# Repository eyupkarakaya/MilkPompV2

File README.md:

# Milk Pomp
Proje, kullanicinin farkli tip ve hacimli bardaklara makineden süt doldurmak için kullanilacak bir cihazin kontrol kartinin tasarlanmasi işidir.

Cihazın mekanik tasarımı, flow sensör ve pompa seçimi müşteri tarafından hazırlanmıştır. Bizim yapacağımız iş ise sistemin çalışmasını sağlayacak elektronik kontrol kartının tasarlanmasıdır.

## Sistemin Çalismasi
Cihaz maksimum 9 farklı bardak bilgisini hafızada tutabilir. Kullanıcı bardak seçimi yaparak kayıtlı bardak tiplerinden birini otomatik olarak doldurabilir. Fakat istenirse kayıtlı olmayan farklı bir kabı da manuel olarak istediği miktarda doldurabilir.

Cihaz üzerinde 3 adet buton ve 1 adet 7-Segment gösterge bulunmaktadır. Ayrıca, bir pulse girişi ile **Akış Sensoru** girişi okunacak ve çıkış olarak bir role kontrol edilecektir.

	* I/O (On/Off) butonu
	* Start butonu
	* Mode butonu
	* Akış Sensoru (Encoder Pulse Input)
	* Role

Aşağıda tarif edilen çalışma şekilleri bu 3 buton ve gösterge kullanılarak gerçeklenecektir.

Sistemi çalıştırmak için I/O butonuna bir kere basıp bırakmak yeterlidir. Sistem kapalıyken gösterge ve diğer butonlar aktif değildir. I/O butonuna bir kere basılıp bırakıldığında sistem açılır, eğer kalibrasyon yapılmamışsa (hiç bardak tanımı yoksa) **C.** değeri görünür ve ekran yanıp söner. Aksi halde sabit olarak **0** yazar ve bardak seçimi için bekler.

Cihaz 3 farklı çalışma şekline sahip olacaktır.

### Kalibrasyon
Kalibrasyon modu, elimizde bulunan bardakların tanımlanması için kullanılır. Maksimum 9 farklı bardak tanımı yapılabilir.

Kalibrasyon modu bir adet bardak tanıtmak istenirse aşağıdaki algoritmaya göre çalışır

	1- Kalibrasyonu başlatmak için I/O butonuna 5 saniye basılı tutulur
	2- Gösterge 0 değerini gösterir ve nokta yanıp sönmeye başlar
	3- İstenilen bardak, cihazın bardak bölmesine yerleştirilir
	4- Mode butonu ile bardak seçimi yapılır (1, 2, 3, ..)
	5- Start butonuna basılı tutularak bardak doldurulur
	6- Bardak dolunca Start butonu bırakılır
	7- Start butonu bırakıldığında seçilen bardak ve doldurulan miktar bilgileri otomatik olarak kaydedilir
	8- Kalibrasyon modundan çıkmak için I/O butonuna 5 saniye bayunca basılır
	
Eğer birden fazla bardak tanımı yapılmak istenirse yukarıdaki algoritma basamaklarından 1 nolu adım ile kalibrasyon işlemi başlatılır. 2-7 adımları her bir bardak için tekrarlanır. Tüm bardakların tanımlanma işlemi bittiğinde 8 nolu adım ile kalibrasyon işlemi sonlandırılır.

Daha sonra tanımlı bir bardağın kalibrasyonu değiştirilmek istendiğinde veya yeni bir bardak tanımı yapılması gerektiğinde yukarıdaki algoritma tekrar uygulanabilir.

> Dikkat edilmesi gereken nokta, eğer bardak tanımları yapılmış bir cihazda tek bir bardağın kalibrasyonu değiştirlmek istenirse, Mode butonu ile doğru bardak numarasının seçildiğinden emin olunması gerekmektedir.

### Otomatik Mod
Kalibrasyonu yapılmış bir cihazda kullanıcı bardak seçimi yaparak tanımlı bardaklardan birini otomatik olarak doldurabilir.

	1- İstenilen bardak, cihazın bardak bölmesine yerleştirilir
	2- Mode butonu kullanılarak bardak seçimi yapılır
	3- Start butonuna basılıp bırakıldığında tanımlı miktar kadar dolum yapılır
	
Her bir bardak için yukarıdaki adımlar tekrarlanır.

### Manuel Mod
Kalibrasyon yapılarak tanımlanmamış bir bardak veya farklı bir kap doldurulmak istendiğinde Manuel mod kullanılır.

    1- Doldurulmak istenilen kap yerleştirilir.
	2- Start butonuna basılı tutulur. Butona basıldıktan 5 saniye sonra manuel dolum başlar
	3- Kullanıcı Start butonunu bıraktığında dolum işlemi sonlanır.

## Kaynak/Arastirmalar
- [Flow Sensor](https://www.hepsiburada.com/fluidotech-kahve-makinasi-pompasi-rotary-pompa-pirinc-govdeli-p-HBV000007SB1Q)
- [Flow Sensor Kullanimi](https://how2electronics.com/iot-water-flow-meter-using-esp8266-water-flow-sensor/)
- [ESP8266 With Water Flow Sensor](https://www.14core.com/wiring-esp8266-1212e-with-g12-liquid-water-flow-sensor-for-wireless-monitoring/)

## Kullanilacak Bilesenler
- [STM32G030F6P6TR](docs/DS12991.pdf) 
- [Relay](http://www.omron.com/ecb/products/pdf/en-g5le.pdf)
- [Display](https://docs.broadcom.com/docs/AV02-2553EN)
- [TLP291](https://toshiba.semicon-storage.com/info/docget.jsp?did=12884&prodName=TLP291)
- Buttons
- Buzzer 
- Resistors
- Capasitors
- Transistors
- Leds
## Algoritma Adimlari
    1) Basla
	2) I/O Butonuna bir kere basarak sistemi ac (Diger hersey pasif olmali)
	3) Eger Kalibrasyon yapilmamissa C.yanip soner once kalibrasyon yapilmali. Eger Kalibrasyon yapilmissa 14.adima git(ilk acilis icin gecerli)
	4) Kalibrasyonu başlatmak için I/O butonuna 5 saniye basılı tutulur
	5) Gösterge 0 değerini gösterir ve nokta yanıp sönmeye başlar
	6) İstenilen bardak, cihazın bardak bölmesine yerleştirilir
	7) Mode butonu ile bardak seçimi yapılır (1, 2, 3, ..)
	8) Start butonuna basılı tutularak bardak doldurulur
	9) Bardak dolunca Start butonu bırakılır
	10) Start butonu bırakıldığında seçilen bardak ve doldurulan miktar bilgileri otomatik olarak kaydedilir
	11) Kalibrasyon modundan çıkmak için I/O butonuna 5 saniye bayunca basılır
	12) Max 9 bardak tanimlanibilir, tanimlanma islemi bittikten sonra 11 adimla islem tamamlanir
	13) Eger birden fazla bardak tanimi yapilmak istenilirse 4 adimdan baslayip 5-11 arasi adimlar tekrarlanir
	14) Eger kalibrasyon yapilmissa ekranda 0 yazar ve bekler
	15) Iki farkli sekilde bardak doldurabilir otomatik ve manuel biri secilir
	16) Eger otomatik ise islem soyle devam eder
	17) İstenilen bardak, cihazın bardak bölmesine yerleştirilir
	18) Mode butonu kullanılarak bardak seçimi yapılır(ornek 1.bardak 0-100ml alir,2.bardak 200-300ml alir)
	19) Start butonuna basılıp bırakıldığında tanımlı miktar kadar dolum yapılır her bardak icin islem tekrar edilir
	20) Eger manuel ise oldurulmak istenilen kap yerleştirilir
	21) Start butonuna basılı tutulur. Butona basıldıktan 5 saniye sonra manuel dolum başlar
	22) Kullanıcı Start butonunu bıraktığında dolum işlemi sonlanır
   
## Algoritma Akış Şeması

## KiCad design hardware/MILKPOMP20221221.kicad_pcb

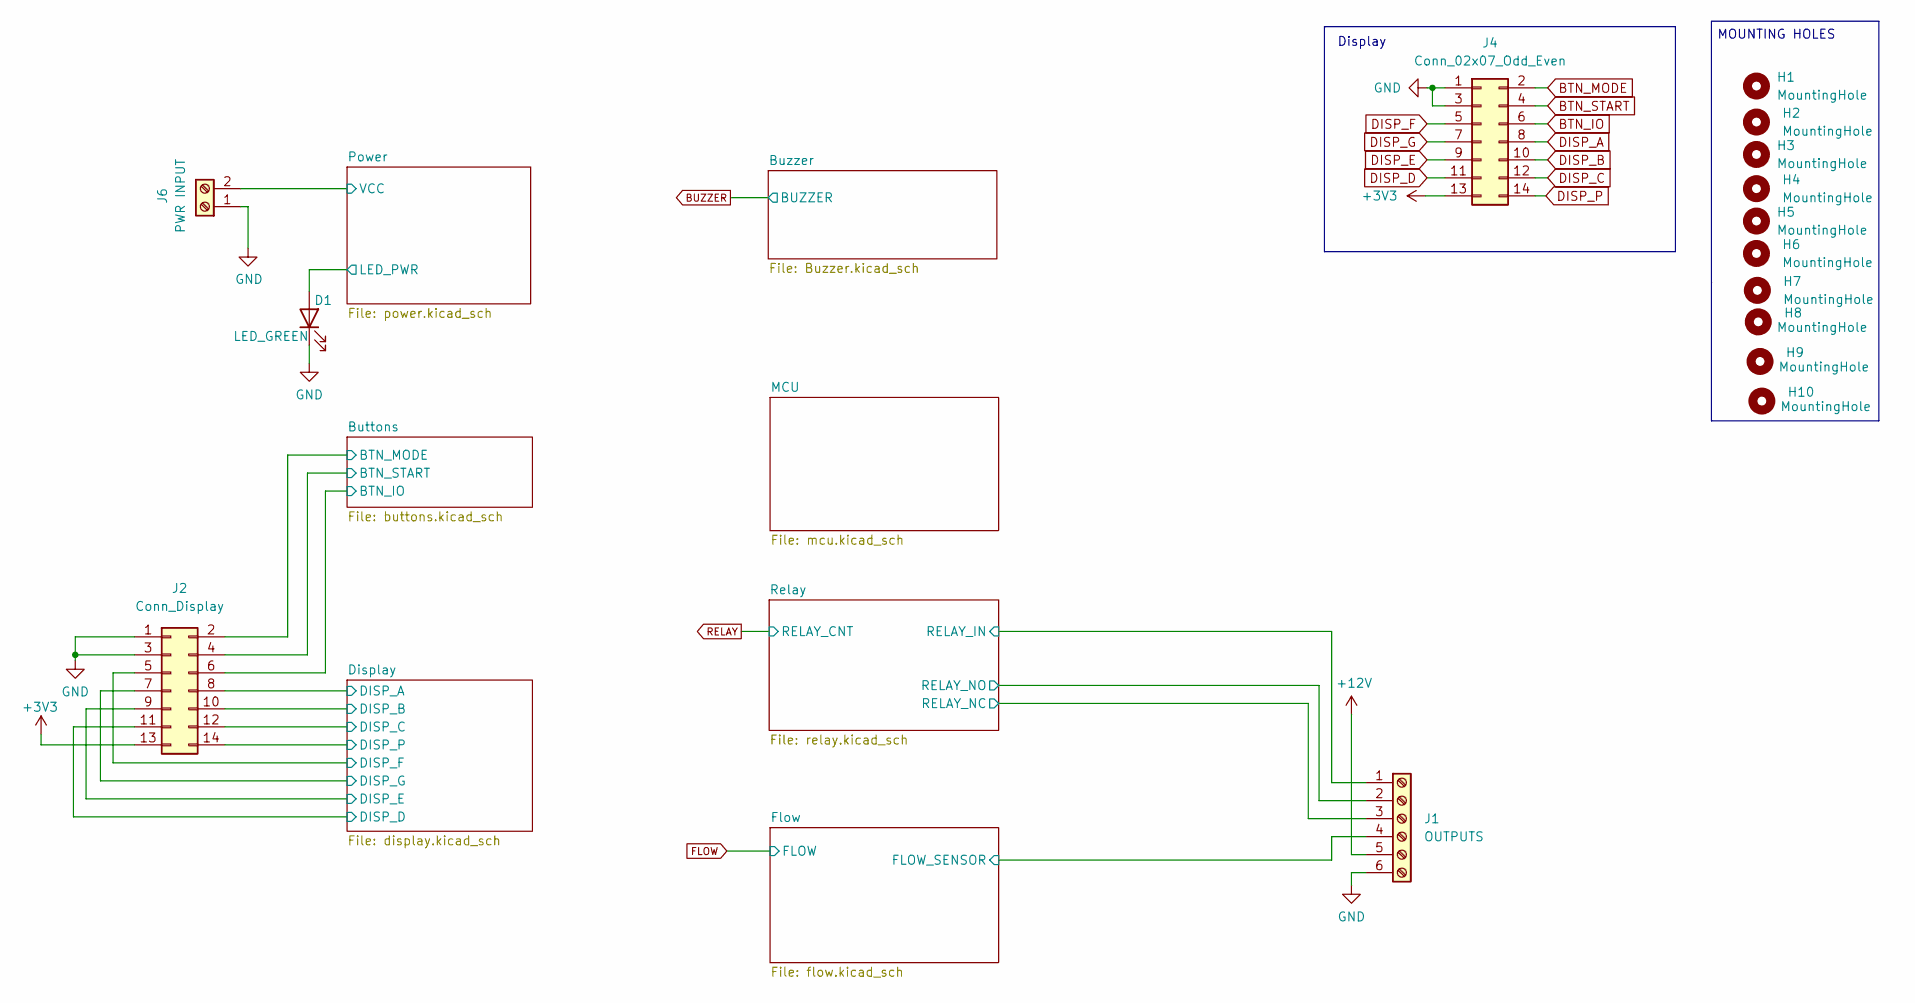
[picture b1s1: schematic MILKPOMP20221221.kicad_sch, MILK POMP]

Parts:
D1: LED_GREEN; LED_1206_3216Metric
H1, H2, H3, H4, H5, H6, H7, H8, H9, H10: MountingHole; MountingHole_2.5mm
J1: OUTPUTS; PhoenixContact_MSTBA_2,5_6-G-5,08_1x06_P5.08mm_Horizontal
J2: Conn_Display; Multicomp_MC9A12-1434_2x07x2.54mm_Straight
J4: Conn_02x07_Odd_Even; Multicomp_MC9A12-1434_2x07x2.54mm_Straight
J6: PWR INPUT; PhoenixContact_MSTBA_2,5_2-G_1x02_P5.00mm_Horizontal

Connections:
+3V3: J2.13, J4.13; also elsewhere on the board
+12V: J1.5, J6.2; also elsewhere on the board
/Buttons/BTN_IO: J2.6; also elsewhere on the board
/Buttons/BTN_MODE: J2.2; also elsewhere on the board
/Buttons/BTN_START: J2.4; also elsewhere on the board
/Display/DISP_A: J2.8; also elsewhere on the board
/Display/DISP_B: J2.10; also elsewhere on the board
/Display/DISP_C: J2.12; also elsewhere on the board
/Display/DISP_D: J2.11; also elsewhere on the board
/Display/DISP_E: J2.9; also elsewhere on the board
/Display/DISP_F: J2.5; also elsewhere on the board
/Display/DISP_G: J2.7; also elsewhere on the board
/Display/DISP_P: J2.14; also elsewhere on the board
/Flow/FLOW_SENSOR: J1.4; also elsewhere on the board
/Power/LED_PWR: D1.2 (A); also elsewhere on the board
/Relay /RELAY_IN: J1.1; also elsewhere on the board
/Relay /RELAY_NC: J1.3; also elsewhere on the board
/Relay /RELAY_NO: J1.2; also elsewhere on the board
BTN_IO: J4.6; also elsewhere on the board
BTN_MODE: J4.2; also elsewhere on the board
BTN_START: J4.4; also elsewhere on the board
DISP_A: J4.8; also elsewhere on the board
DISP_B: J4.10; also elsewhere on the board
DISP_C: J4.12; also elsewhere on the board
DISP_D: J4.11; also elsewhere on the board
DISP_E: J4.9; also elsewhere on the board
DISP_F: J4.5; also elsewhere on the board
DISP_G: J4.7; also elsewhere on the board
DISP_P: J4.14; also elsewhere on the board
GND: D1.1 (K), J1.6, J2.1, J2.3, J4.1, J4.3, J6.1; also elsewhere on the board

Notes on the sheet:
Display
MOUNTING HOLES

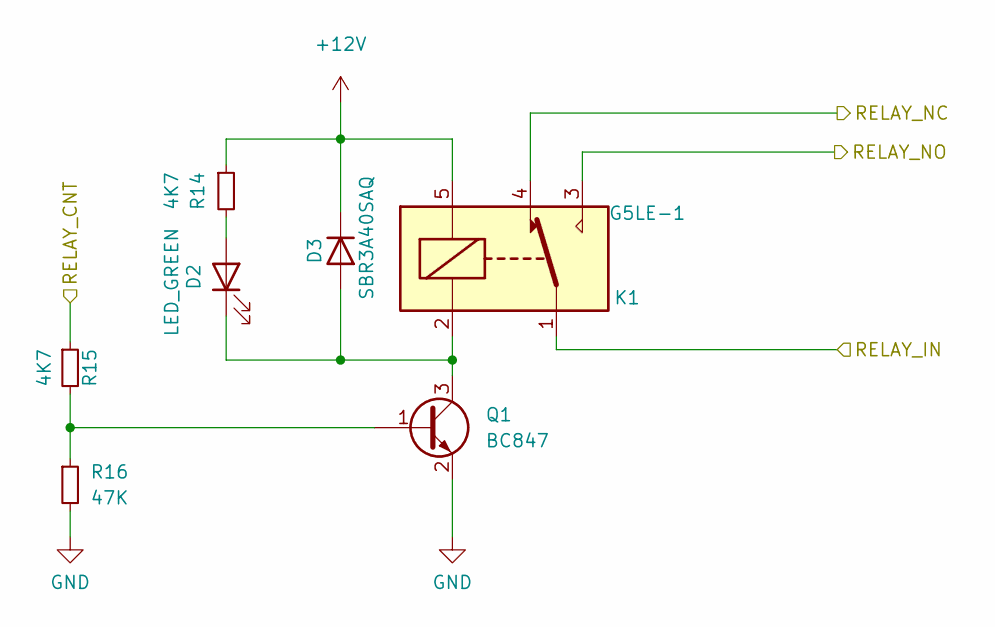
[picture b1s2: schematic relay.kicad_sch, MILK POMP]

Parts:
D2: LED_GREEN; LED_1206_3216Metric
D3: SBR3A40SAQ; D_SMB_Handsoldering; DIGIKEY_PART_NUMBER SBR3A40SAQ-13DICT-ND
K1: G5LE-1; Relay_SPDT_Omron-G5LE-1
Q1: BC847; SOT-23
R14, R15: 4K7; R_0603_1608Metric
R16: 47K; R_0603_1608Metric

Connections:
+12V: D3.1 (K), K1.5, R14.1; also elsewhere on the board
/Relay /RELAY_IN: K1.1; also elsewhere on the board
/Relay /RELAY_NC: K1.4; also elsewhere on the board
/Relay /RELAY_NO: K1.3; also elsewhere on the board
GND: Q1.2 (E), R16.2; also elsewhere on the board
unnamed: D2.1 (K), D3.2 (A), K1.2, Q1.3 (C)
unnamed: D2.2 (A), R14.2
unnamed: Q1.1 (B), R15.2, R16.1
RELAY: R15.1; also elsewhere on the board

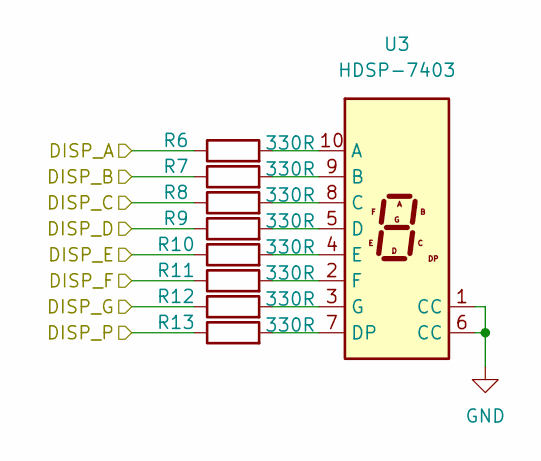
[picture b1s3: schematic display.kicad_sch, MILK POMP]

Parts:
R6, R7, R8, R9, R10, R11, R12, R13: 330R; R_0603_1608Metric
U3: HDSP-7403; HDSP-7401

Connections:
/Display/DISP_A: R6.1; also elsewhere on the board
/Display/DISP_B: R7.1; also elsewhere on the board
/Display/DISP_C: R8.1; also elsewhere on the board
/Display/DISP_D: R9.1; also elsewhere on the board
/Display/DISP_E: R10.1; also elsewhere on the board
/Display/DISP_F: R11.1; also elsewhere on the board
/Display/DISP_G: R12.1; also elsewhere on the board
/Display/DISP_P: R13.1; also elsewhere on the board
GND: U3.1 (CC), U3.6 (CC); also elsewhere on the board
unnamed: R6.2, U3.10 (A)
unnamed: R7.2, U3.9 (B)
unnamed: R8.2, U3.8 (C)
unnamed: R9.2, U3.5 (D)
unnamed: R10.2, U3.4 (E)
unnamed: R11.2, U3.2 (F)
unnamed: R12.2, U3.3 (G)
unnamed: R13.2, U3.7 (DP)

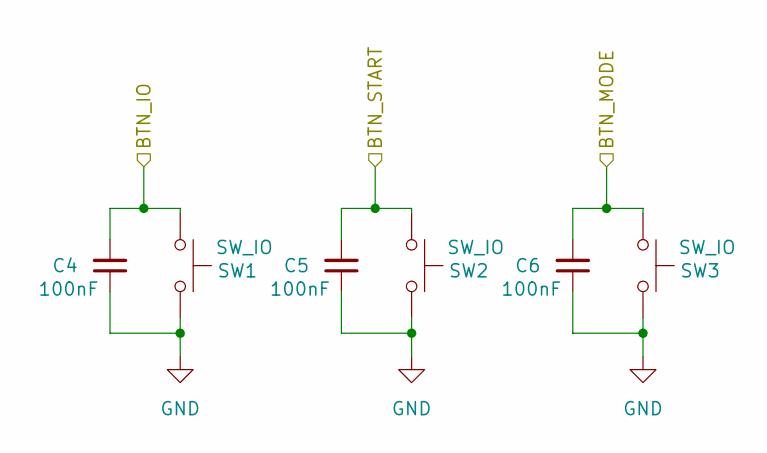
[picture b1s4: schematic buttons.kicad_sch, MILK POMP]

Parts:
C4, C5, C6: 100nF; C_0603_1608Metric
SW1, SW2, SW3: SW_IO; SW_PUSH-12mm

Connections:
/Buttons/BTN_IO: C4.2, SW1.1; also elsewhere on the board
/Buttons/BTN_MODE: C6.2, SW3.1; also elsewhere on the board
/Buttons/BTN_START: C5.2, SW2.1; also elsewhere on the board
GND: C4.1, C5.1, C6.1, SW1.2, SW2.2, SW3.2; also elsewhere on the board

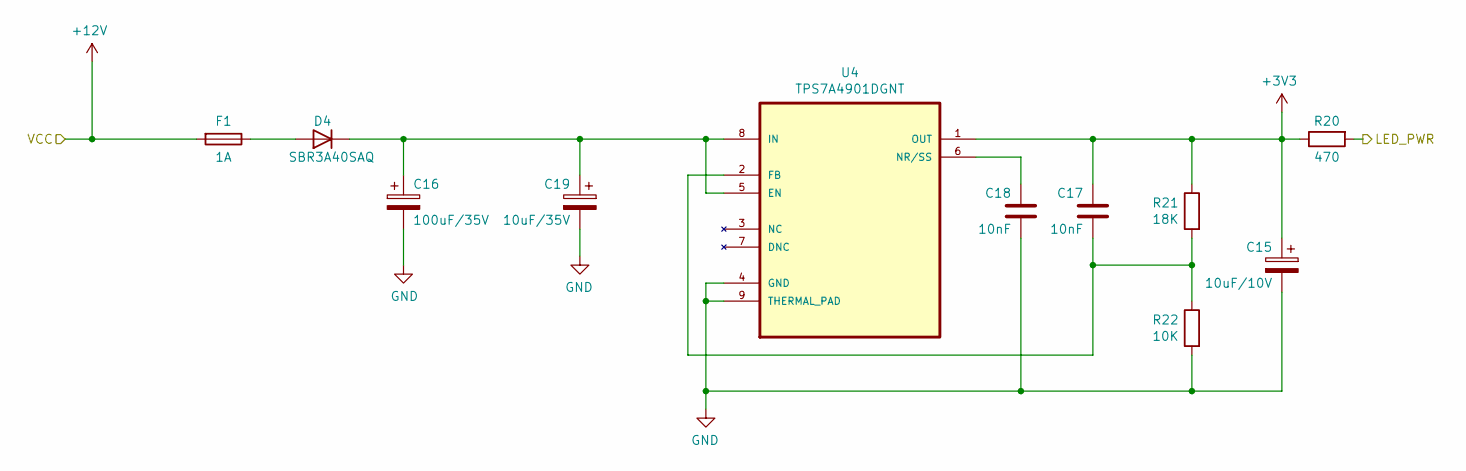
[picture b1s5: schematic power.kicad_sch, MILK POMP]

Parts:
C15: 10uF/10V; CP_Elec_6.3x7.7; Digikey 10-EEE-FN1A100RDKR-ND
C16: 100uF/35V; CP_Elec_10x10.5; Digikey PCE3951TR-ND
C17, C18: 10nF; C_0603_1608Metric; Digikey 1276-CL10B103KB8WPJCDKR-ND
C19: 10uF/35V; CP_Elec_6.3x7.7; Digikey 10-EEE-FN1A100RDKR-ND
D4: SBR3A40SAQ; D_SMB_Handsoldering; DIGIKEY_PART_NUMBER SBR3A40SAQ-13DICT-ND
F1: 1A; Fuse_1206_3216Metric; Digikey F2881CT-ND
R20: 470; R_0603_1608Metric; Digikey YAG1301DKR-ND
R21: 18K; R_0603_1608Metric; Digikey YAG3570DKR-ND
R22: 10K; R_0603_1608Metric; Digikey 311-10.0KHRDKR-ND
U4: TPS7A4901DGNT; SOP65P490X110-9N; MPN TPS7A4901DGNT; Digikey 296-27769-6-ND

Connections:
+3V3: C15.1, C17.1, R20.1, R21.1, U4.1 (OUT); also elsewhere on the board
+12V: F1.2; also elsewhere on the board
/Power/LED_PWR: R20.2; also elsewhere on the board
GND: C15.2, C16.2, C18.2, C19.2, R22.2, U4.4 (GND), U4.9 (THERMAL_PAD); also elsewhere on the board
unnamed: C16.1, C19.1, D4.1 (K), U4.5 (EN), U4.8 (IN)
unnamed: C17.2, R21.2, R22.1, U4.2 (FB)
unnamed: C18.1, U4.6 (NR/SS)
unnamed: D4.2 (A), F1.1

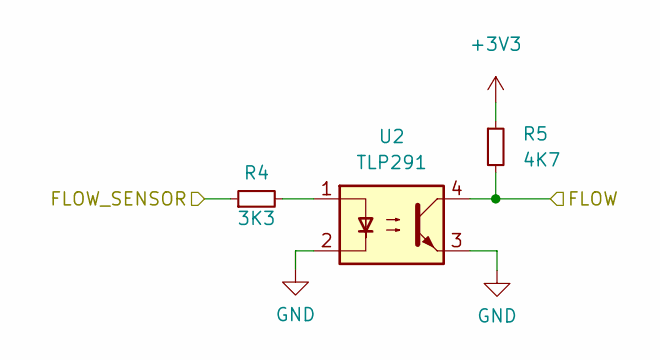
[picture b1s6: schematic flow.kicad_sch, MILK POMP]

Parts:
R4: 3K3; R_0603_1608Metric
R5: 4K7; R_0603_1608Metric
U2: TLP291; SOIC-4_4.55x2.6mm_P1.27mm

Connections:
+3V3: R5.1; also elsewhere on the board
/Flow/FLOW_SENSOR: R4.1; also elsewhere on the board
FLOW: R5.2, U2.4; also elsewhere on the board
GND: U2.2, U2.3; also elsewhere on the board
unnamed: R4.2, U2.1

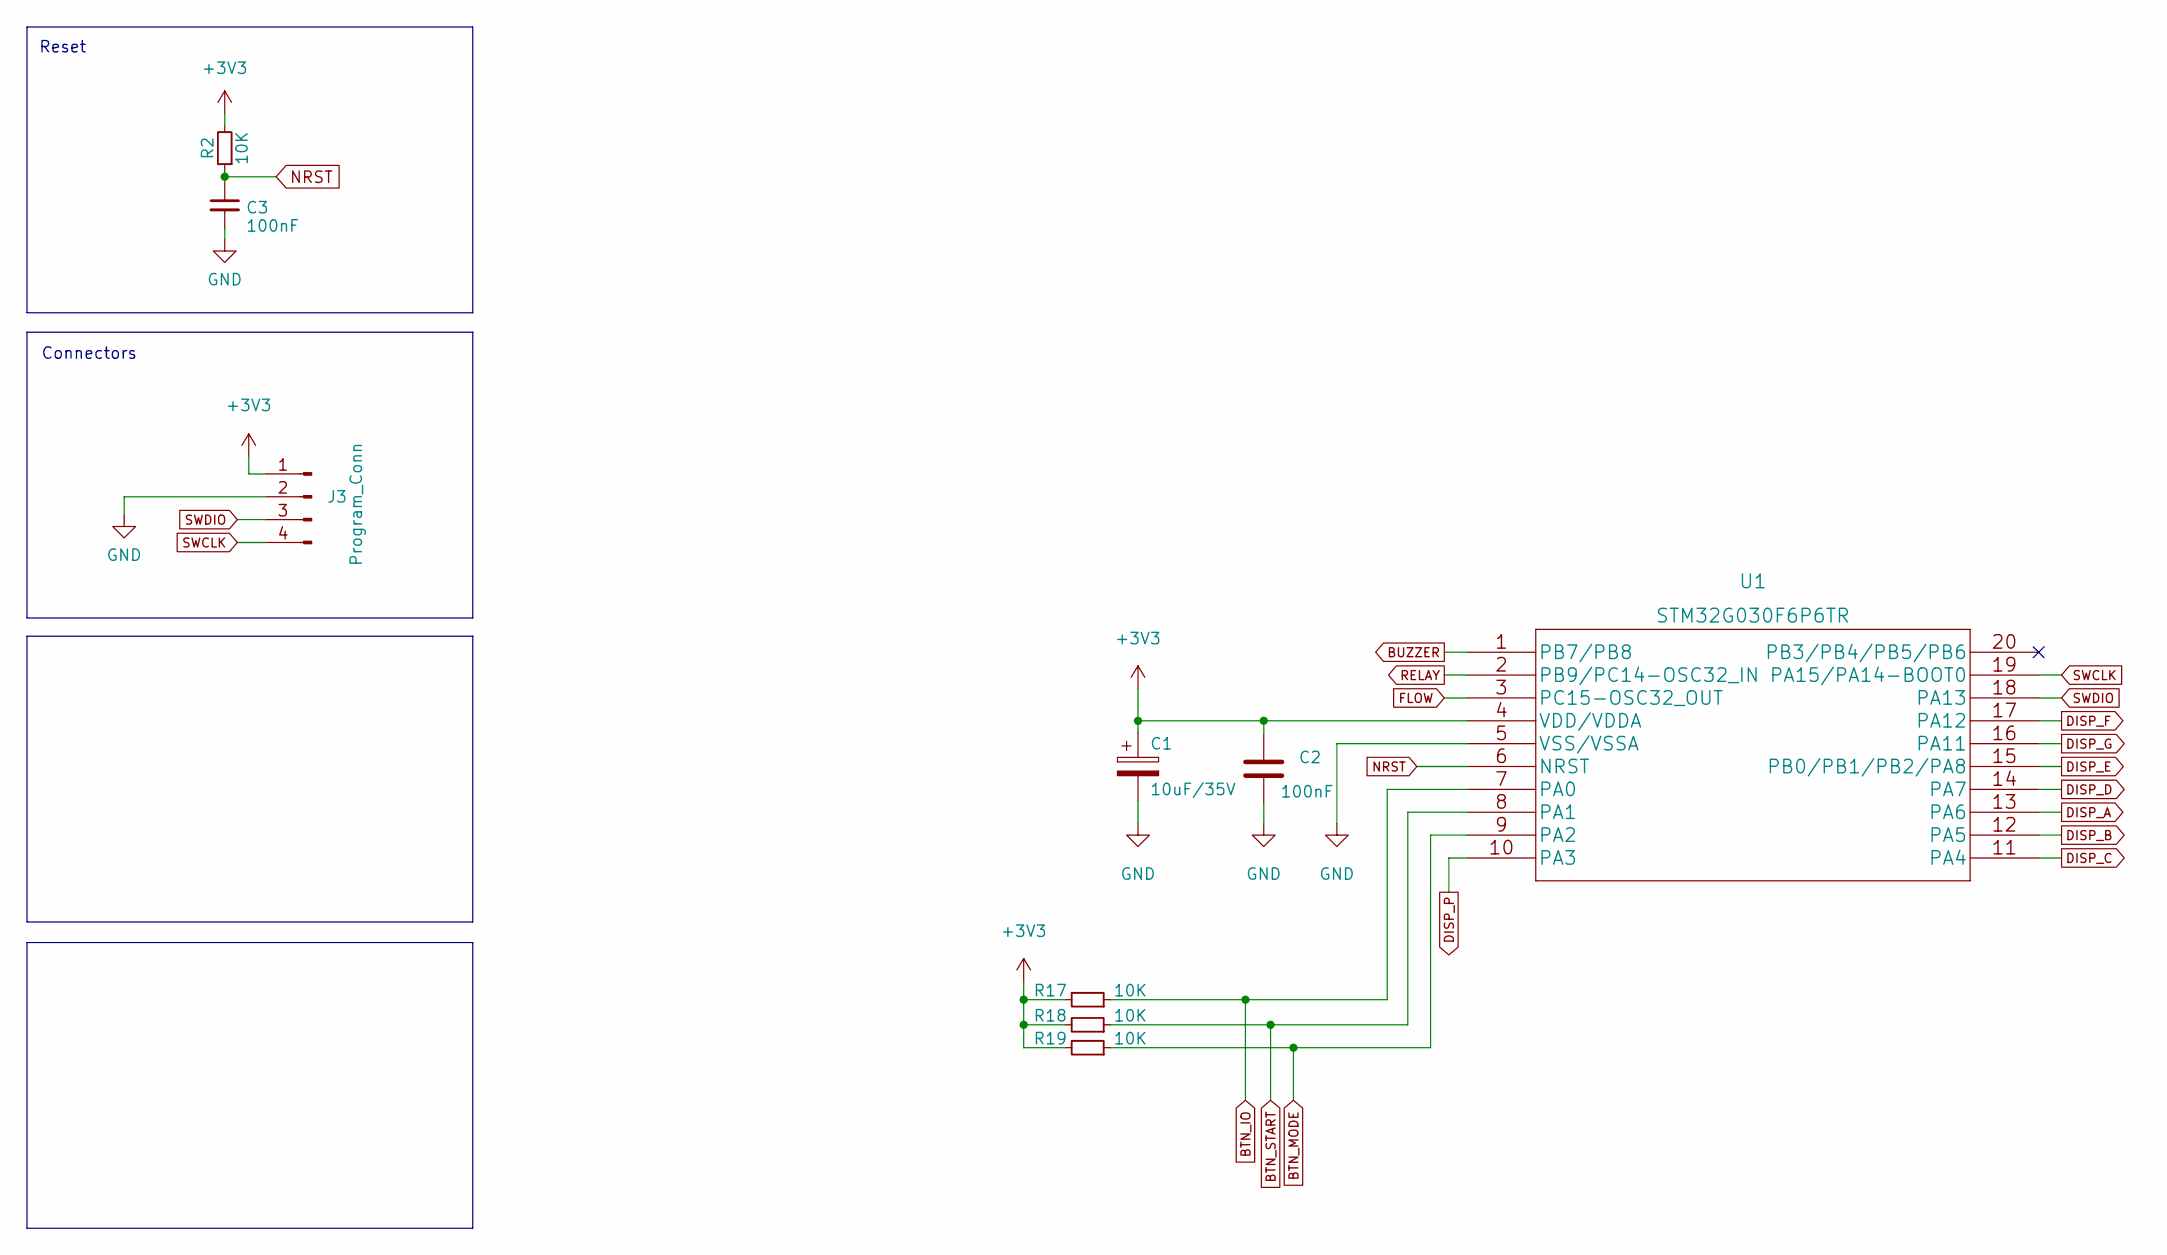
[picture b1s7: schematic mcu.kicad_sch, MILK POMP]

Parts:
C1: 10uF/35V; CP_Elec_6.3x7.7; Digikey 10-EEE-FN1A100RDKR-ND
C2: 100nF; C_0603_1608Metric; Digikey AC0603KPX7R7BB104
C3: 100nF; C_0603_1608Metric
J3: Program_Conn; PinHeader_1x04_P2.54mm_Vertical
R2, R17, R18, R19: 10K; R_0603_1608Metric
U1: STM32G030F6P6TR; SOP65P640X120-20N

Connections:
+3V3: C1.1, C2.1, J3.1, R2.2, R17.2, R18.2, R19.2, U1.4 (VDD/VDDA); also elsewhere on the board
BTN_IO: R17.1, U1.7 (PA0); also elsewhere on the board
BTN_MODE: R19.1, U1.9 (PA2); also elsewhere on the board
BTN_START: R18.1, U1.8 (PA1); also elsewhere on the board
BUZZER: U1.1 (PB7/PB8); also elsewhere on the board
DISP_A: U1.13 (PA6); also elsewhere on the board
DISP_B: U1.12 (PA5); also elsewhere on the board
DISP_C: U1.11 (PA4); also elsewhere on the board
DISP_D: U1.14 (PA7); also elsewhere on the board
DISP_E: U1.15 (PB0/PB1/PB2/PA8); also elsewhere on the board
DISP_F: U1.17 (PA12); also elsewhere on the board
DISP_G: U1.16 (PA11); also elsewhere on the board
DISP_P: U1.10 (PA3); also elsewhere on the board
FLOW: U1.3 (PC15-OSC32_OUT); also elsewhere on the board
GND: C1.2, C2.2, C3.2, J3.2, U1.5 (VSS/VSSA); also elsewhere on the board
NRST: C3.1, R2.1, U1.6 (NRST)
RELAY: U1.2 (PB9/PC14-OSC32_IN); also elsewhere on the board
SWCLK: J3.4, U1.19 (PA15/PA14-BOOT0)
SWDIO: J3.3, U1.18 (PA13)

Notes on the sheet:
Connectors
Reset

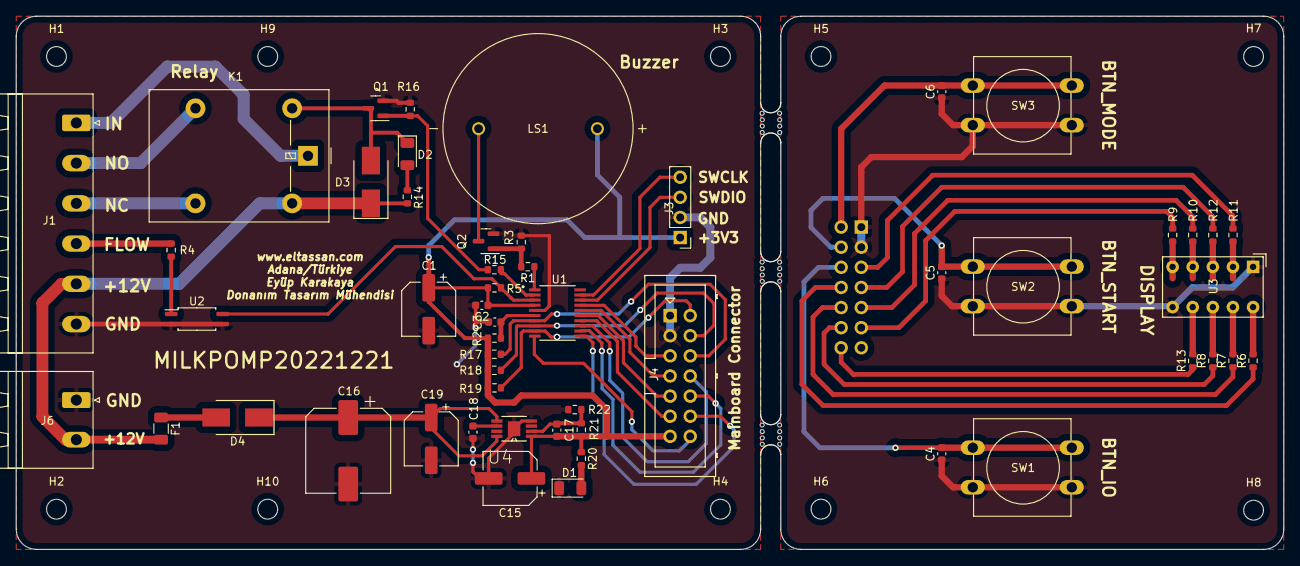
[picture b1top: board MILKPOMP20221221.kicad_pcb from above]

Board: 2 copper layers, 160.0 x 67.3 mm, 67 parts (1 on the bottom side), 54 nets.

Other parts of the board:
LS1: KPEG228; XDCR_KPEG228
Q2: BC847; SOT-23
R1: 4K7; R_0603_1608Metric
R3: 47K; R_0603_1608Metric
mouse-bite-2.54mm-slot, mouse-bite-2.54mm-slot#2, mouse-bite-2.54mm-slot#3: VAL**; mouse-bite-2.54mm-slot

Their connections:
+3V3: LS1.P; also elsewhere on the board
BUZZER: R1.1; also elsewhere on the board
GND: Q2.2 (E), R3.2; also elsewhere on the board
unnamed: LS1.N, Q2.3 (C)
unnamed: Q2.1 (B), R1.2, R3.1

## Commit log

2022-12-05 second commit
2022-12-05 project name added
2022-12-05 PCB arranged
2022-12-05 Readme file changed
2022-12-05 naming is complete
2022-12-05 gerber files chanced
2022-12-06 arrangement has been made
2023-01-09 name stardandi added, readme file updated
2023-01-09 readme file updated
2023-01-10 flow chart added
